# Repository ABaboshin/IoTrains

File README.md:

# IoTrains

Internet of Trains :)

The existing systems in the market are either with old roots (DCC) or not opensource (Märklin). More then that they were built over 20 years ago and therefore have historical restrictions. In order to be able more flexible I started to write a firmware for the trains and accessories using ESP32/ESP8266.

The projects consists of:
 - [Firmware](./firmware/) which is written in c++ using PlatformIO,
 - MQTT Broker, see [emqx](./emqx) as an example,
 - A [backend](./webui/server) written in typesript,
 - as well [frontend](./webui/client/) in react,
 - [json schema](./jsonschema/) describes a mqtt based protocol.

# License
The source code and schematic are licensed under MIT license.

The train's STL files are licensed under CC BY-NC-SA 4.0.

# Notes
 - Connect an audio amplifier to an i2s capable pin i.e. DAC_1.

## TODO
 - multiple rfid
 - responsive ui / refresh on update
 - process rfid events
 - sqlite3
 - main board max 4 x 2.3 c

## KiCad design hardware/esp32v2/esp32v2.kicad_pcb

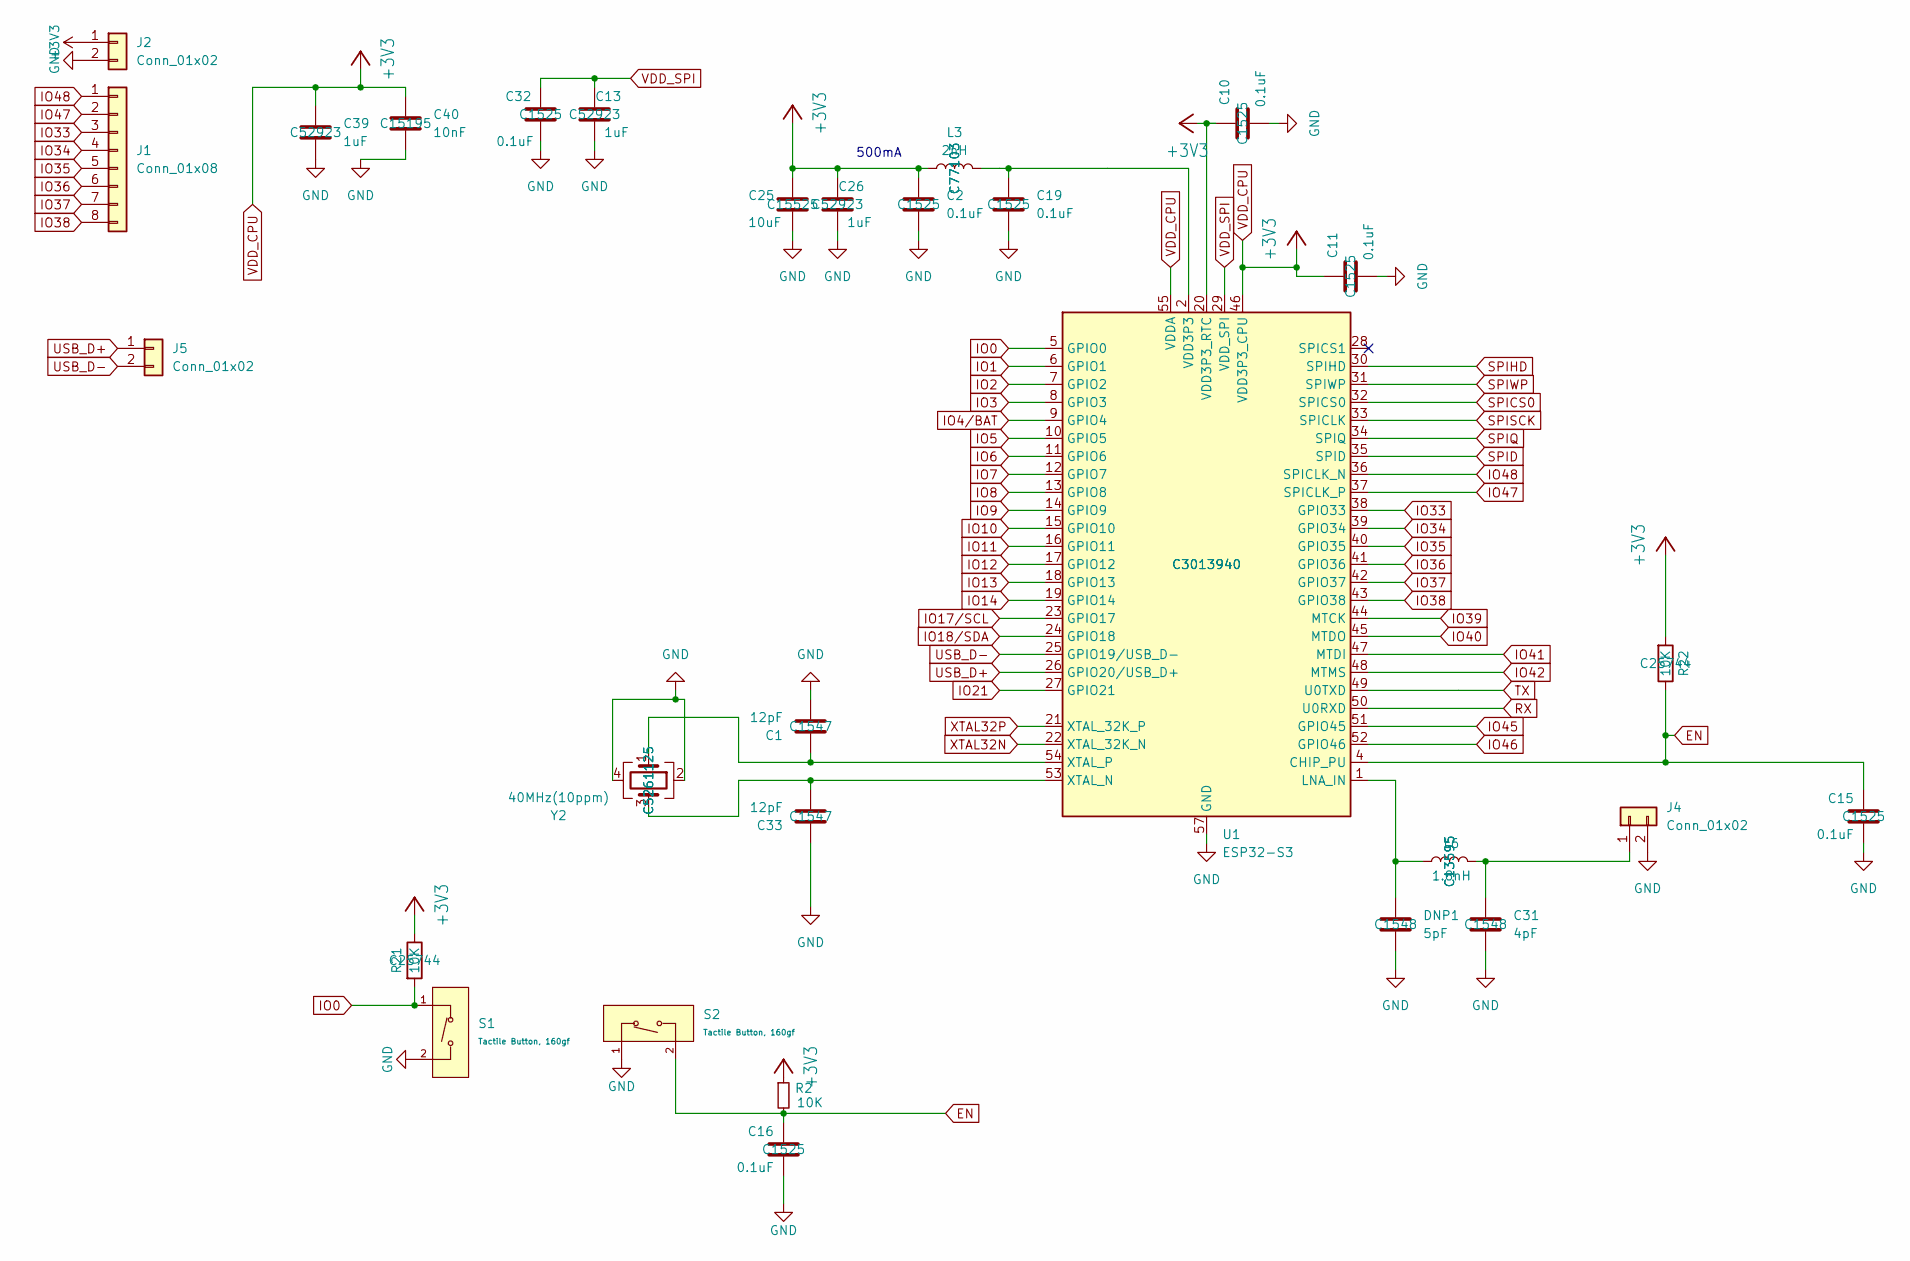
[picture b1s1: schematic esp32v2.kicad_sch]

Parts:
C1, C33: 12pF; C_0201_0603Metric; MNF PART NUMBER C1547; LCSC C1547
C2, C10, C11, C15, C16, C19, C32: 0.1uF; C_0201_0603Metric; MNF PART NUMBER C1525; LCSC C1525
C13, C26, C39: 1uF; C_0201_0603Metric; MNF PART NUMBER C52923; LCSC C52923
C25: 10uF; C_0201_0603Metric; MNF PART NUMBER C15525; LCSC C15525
C31: 4pF; C_0201_0603Metric; MNF PART NUMBER C1548; LCSC C1548
C40: 10nF; C_0201_0603Metric; MNF PART NUMBER C15195; LCSC C15195
DNP1: 5pF; C_0201_0603Metric; MNF PART NUMBER C1548; LCSC C1548
J1: Conn_01x08; JST_SHL_SM08B-SHLS-TF_1x08-1MP_P1.00mm_Horizontal
J2: Conn_01x02; S2BZRLFSN; LCSC C157930
J4: Conn_01x02; U.FL_Molex_MCRF_73412-0110_Vertical
J5: Conn_01x02; JST_SH_BM02B-SRSS-TB_1x02-1MP_P1.00mm_Vertical; LCSC C157930
L3: 2nH; L_0201_0603Metric; MNF PART NUMBER C77103; LCSC C77103
L6: 1.8nH; L_0201_0603Metric; MNF PART NUMBER C13595; LCSC C13595
R2: 10K; R_0201_0603Metric
R21, R22: 10K; R_0201_0603Metric; MNF PART NUMBER C25744; LCSC C25744
S1, S2: Tactile Button, 160gf; SW_TS-1088-AR02016; Voltage Rating (Dc) 12V; Part TS-1088-AR02016; LCSC C720477
U1: ESP32-S3; QFN-56-1EP_7x7mm_P0.4mm_EP4x4mm; MNF PART NUMBER C3013940; LCSC C3013940
Y2: 40MHz(10ppm); Crystal_SMD_2520-4Pin_2.5x2.0mm; MNF PART NUMBER C5261125; LCSC C5261125

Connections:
EN: C15.1, C16.1, R2.2, R22.1, S2.2 (B), U1.4 (CHIP_PU)
GND: C1.2, C2.2, C10.2, C11.2, C13.2, C15.2, C16.2, C19.2, C25.2, C26.2, C31.2, C32.2, C33.1, C39.2, C40.2, DNP1.2, J2.2, J4.2, S1.2 (B), S2.1 (A), U1.57 (GND), Y2.2, Y2.4
IO0: R21.2, S1.1 (A), U1.5 (GPIO0)
IO1: U1.6 (GPIO1)
IO2: U1.7 (GPIO2)
IO3: U1.8 (GPIO3)
IO4/BAT: U1.9 (GPIO4)
IO5: U1.10 (GPIO5)
IO6: U1.11 (GPIO6)
IO7: U1.12 (GPIO7)
IO8: U1.13 (GPIO8)
IO9: U1.14 (GPIO9)
IO10: U1.15 (GPIO10)
IO11: U1.16 (GPIO11)
IO12: U1.17 (GPIO12)
IO13: U1.18 (GPIO13)
IO14: U1.19 (GPIO14)
IO17/SCL: U1.23 (GPIO17)
IO18/SDA: U1.24 (GPIO18)
IO21: U1.27 (GPIO21)
IO33: J1.3, U1.38 (GPIO33)
IO34: J1.4, U1.39 (GPIO34)
IO35: J1.5, U1.40 (GPIO35)
IO36: J1.6, U1.41 (GPIO36)
IO37: J1.7, U1.42 (GPIO37)
IO38: J1.8, U1.43 (GPIO38)
IO39: U1.44 (MTCK)
IO40: U1.45 (MTDO)
IO41: U1.47 (MTDI)
IO42: U1.48 (MTMS)
IO45: U1.51 (GPIO45)
IO46: U1.52 (GPIO46)
IO47: J1.2, U1.37 (SPICLK_P)
IO48: J1.1, U1.36 (SPICLK_N)
unnamed: C19.1, L3.2, U1.2 (VDD3P3), U1.3 (VDD3P3)
unnamed: C31.1, J4.1, L6.2
unnamed: DNP1.1, L6.1, U1.1 (LNA_IN)
unnamed: C33.2, U1.53 (XTAL_N), Y2.3
unnamed: C1.1, U1.54 (XTAL_P), Y2.1
RX: U1.50 (U0RXD)
SPICS0: U1.32 (SPICS0)
SPID: U1.35 (SPID)
SPIHD: U1.30 (SPIHD)
SPIQ: U1.34 (SPIQ)
SPISCK: U1.33 (SPICLK)
SPIWP: U1.31 (SPIWP)
TX: U1.49 (U0TXD)
USB_D+: J5.1, U1.26 (GPIO20/USB_D+)
USB_D-: J5.2, U1.25 (GPIO19/USB_D-)
VDD_CPU: C2.1, C10.1, C11.1, C25.1, C26.1, C39.1, C40.1, J2.1, L3.1, R2.1, R21.1, R22.2, U1.20 (VDD3P3_RTC), U1.46 (VDD3P3_CPU), U1.55 (VDDA), U1.56 (VDDA)
VDD_SPI: C13.1, C32.1, U1.29 (VDD_SPI)
XTAL32N: U1.22 (XTAL_32K_N)
XTAL32P: U1.21 (XTAL_32K_P)

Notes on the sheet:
500mA

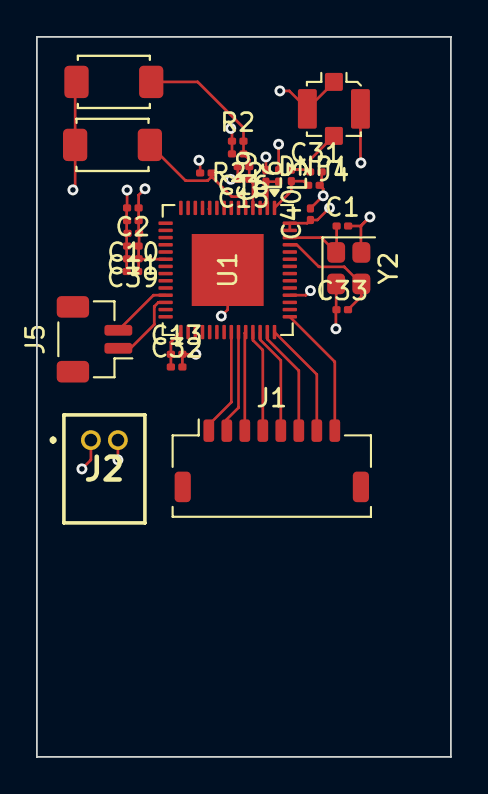
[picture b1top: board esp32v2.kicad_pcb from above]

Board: 4 copper layers, 23.0 x 40.0 mm, 29 parts (0 on the bottom side), 20 nets.

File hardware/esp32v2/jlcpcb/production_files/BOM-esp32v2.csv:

Comment,Designator,Footprint,LCSC,Quantity
0.1uF,"C10,C11,C15,C16,C19,C2,C32",C_0201_0603Metric,C1525,7
1.8nH,L6,L_0201_0603Metric,C13595,1
10K,"R21,R22",R_0201_0603Metric,C25744,2
10nF,C40,C_0201_0603Metric,C15195,1
10uF,C25,C_0201_0603Metric,C15525,1
12pF,"C1,C33",C_0201_0603Metric,C1547,2
1uF,"C13,C26,C39",C_0201_0603Metric,C52923,3
2nH,L3,L_0201_0603Metric,C77103,1
40MHz(10ppm),Y2,Crystal_SMD_2520-4Pin_2.5x2.0mm,C5261125,1
4pF,C31,C_0201_0603Metric,C1548,1
5pF,DNP1,C_0201_0603Metric,C1548,1
Conn_01x02,"J2,J5",S2BZRLFSN,C157930,2
ESP32-S3,U1,QFN-56-1EP_7x7mm_P0.4mm_EP4x4mm,C2913194,1
"Tactile Button, 160gf","S1,S2",SW_TS-1088-AR02016,C720477,2
10K,R2,R_0201_0603Metric,,1
Conn_01x08,J1,JST_SHL_SM08B-SHLS-TF_1x08-1MP_P1.00mm_Horizontal,,1
Conn_01x02,J4,U.FL_Molex_MCRF_73412-0110_Vertical,,1

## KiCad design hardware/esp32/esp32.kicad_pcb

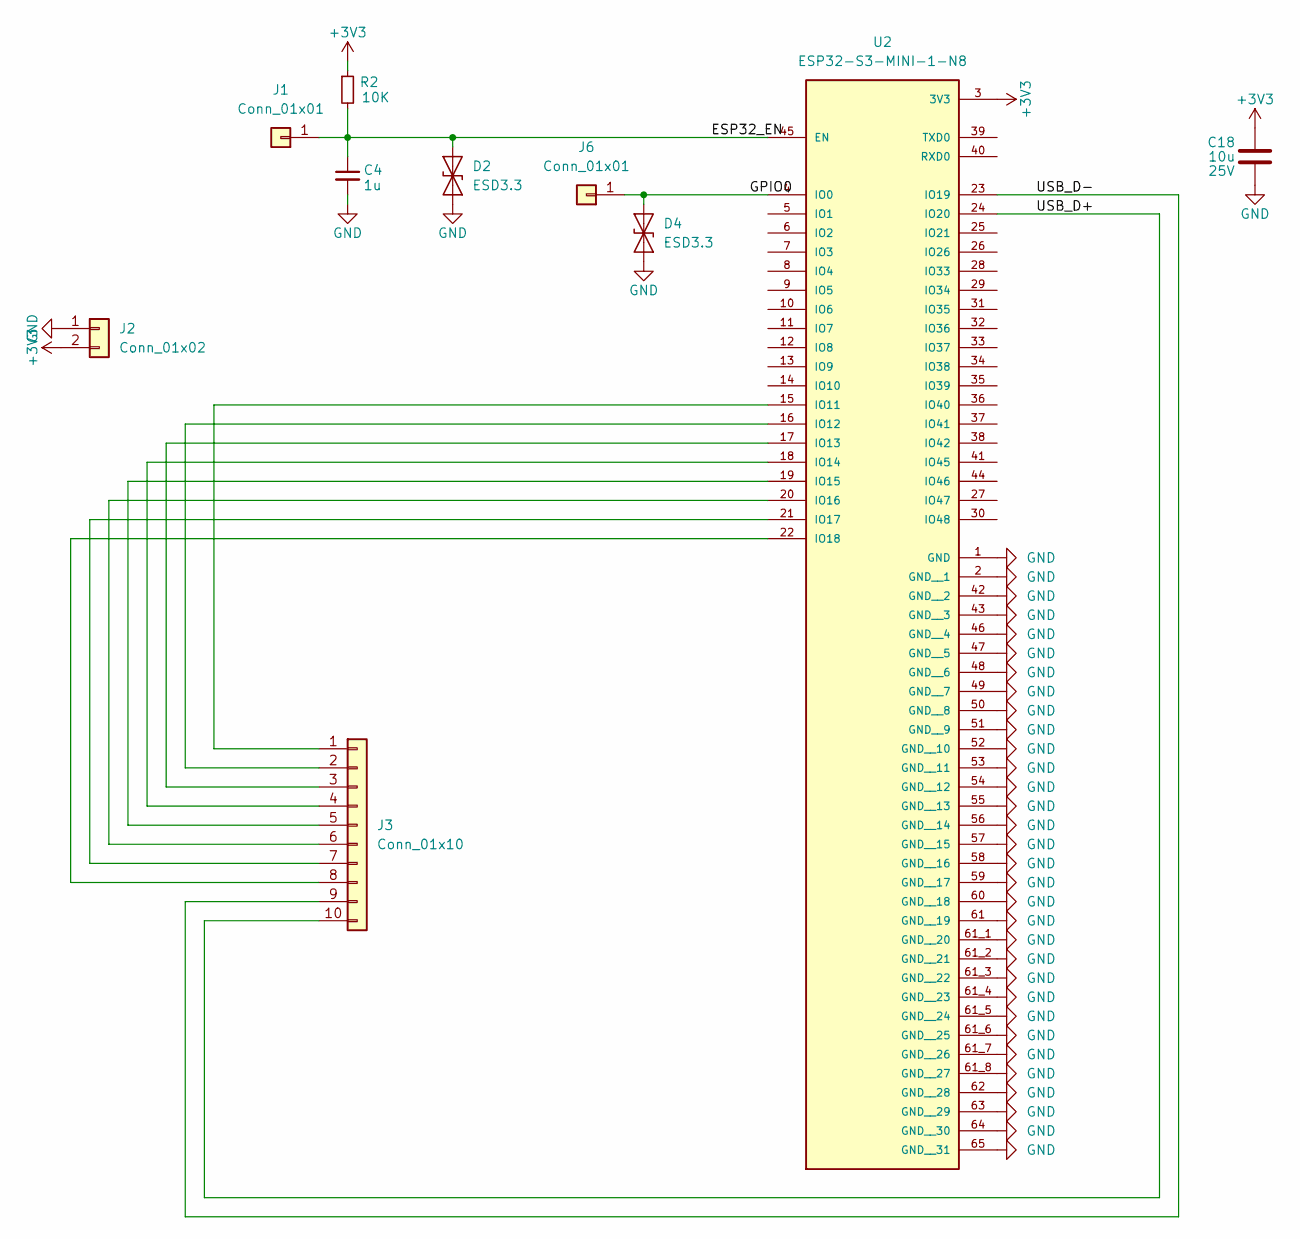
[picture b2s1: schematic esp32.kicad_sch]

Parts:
C4: 1u; C_0603_1608Metric
C18: 10u; C_0603_1608Metric; Voltage 25V; LCSC Part # C96446
D2, D4: ESD3.3; SOT-723
J1, J6: Conn_01x01; PinHeader_1x01_P1.00mm_Vertical
J2: Conn_01x02; S2BZRLFSN; LCSC C157930
J3: Conn_01x10; SM10B-SRSS-TB; LCSC C160409
R2: 10K; R_0402_1005Metric
U2: ESP32-S3-MINI-1-N8; XCVR_ESP32-S3-MINI-1-N8; PARTREV v0.6

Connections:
+3V3: C18.1, J2.2, R2.1, U2.3 (3V3)
/ESP32_EN: C4.1, D2.2 (A2), J1.1, R2.2, U2.45 (EN)
/GPIO0: D4.2 (A2), J6.1, U2.4 (IO0)
/USB_D+: J3.10, U2.24 (IO20)
/USB_D-: J3.9, U2.23 (IO19)
GND: C4.2, C18.2, D2.1 (A1), D4.1 (A1), J2.1, U2.1 (GND), U2.2 (GND__1), U2.42 (GND__2), U2.43 (GND__3), U2.46 (GND__4), U2.47 (GND__5), U2.48 (GND__6), U2.49 (GND__7), U2.50 (GND__8), U2.51 (GND__9), U2.52 (GND__10), U2.53 (GND__11), U2.54 (GND__12), U2.55 (GND__13), U2.56 (GND__14), U2.57 (GND__15), U2.58 (GND__16), U2.59 (GND__17), U2.60 (GND__18), U2.61 (GND__19), U2.61_1 (GND__20), U2.61_2 (GND__21), U2.61_3 (GND__22), U2.61_4 (GND__23), U2.61_5 (GND__24), U2.61_6 (GND__25), U2.61_7 (GND__26), U2.61_8 (GND__27), U2.62 (GND__28), U2.63 (GND__29), U2.64 (GND__30), U2.65 (GND__31)
unnamed: J3.1, U2.15 (IO11)
unnamed: J3.2, U2.16 (IO12)
unnamed: J3.3, U2.17 (IO13)
unnamed: J3.4, U2.18 (IO14)
unnamed: J3.5, U2.19 (IO15)
unnamed: J3.6, U2.20 (IO16)
unnamed: J3.7, U2.21 (IO17)
unnamed: J3.8, U2.22 (IO18)

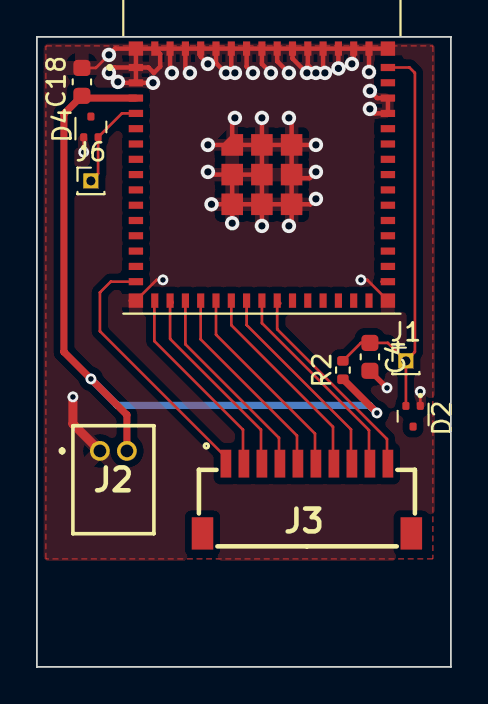
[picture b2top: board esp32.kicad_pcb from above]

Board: 2 copper layers, 23.0 x 35.0 mm, 10 parts (0 on the bottom side), 14 nets.

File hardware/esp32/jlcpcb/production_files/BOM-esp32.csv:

Comment,Designator,Footprint,LCSC,Quantity
10K,R2,R_0402_1005Metric,C25744,1
10u,C18,C_0603_1608Metric,C96446,1
1u,C4,C_0603_1608Metric,C15849,1
Conn_01x02,J2,S2BZRLFSN,C157930,1
Conn_01x10,J3,SM10B-SRSS-TB,C160409,1
ESD3.3,"D2,D4",SOT-723,C233435,2
ESP32-S3-MINI-1-N8,U2,XCVR_ESP32-S3-MINI-1-N8,C2913206,1
Conn_01x01,J1,PinHeader_1x01_P1.00mm_Vertical,,1
Conn_01x01,J6,PinHeader_1x01_P1.00mm_Vertical,,1

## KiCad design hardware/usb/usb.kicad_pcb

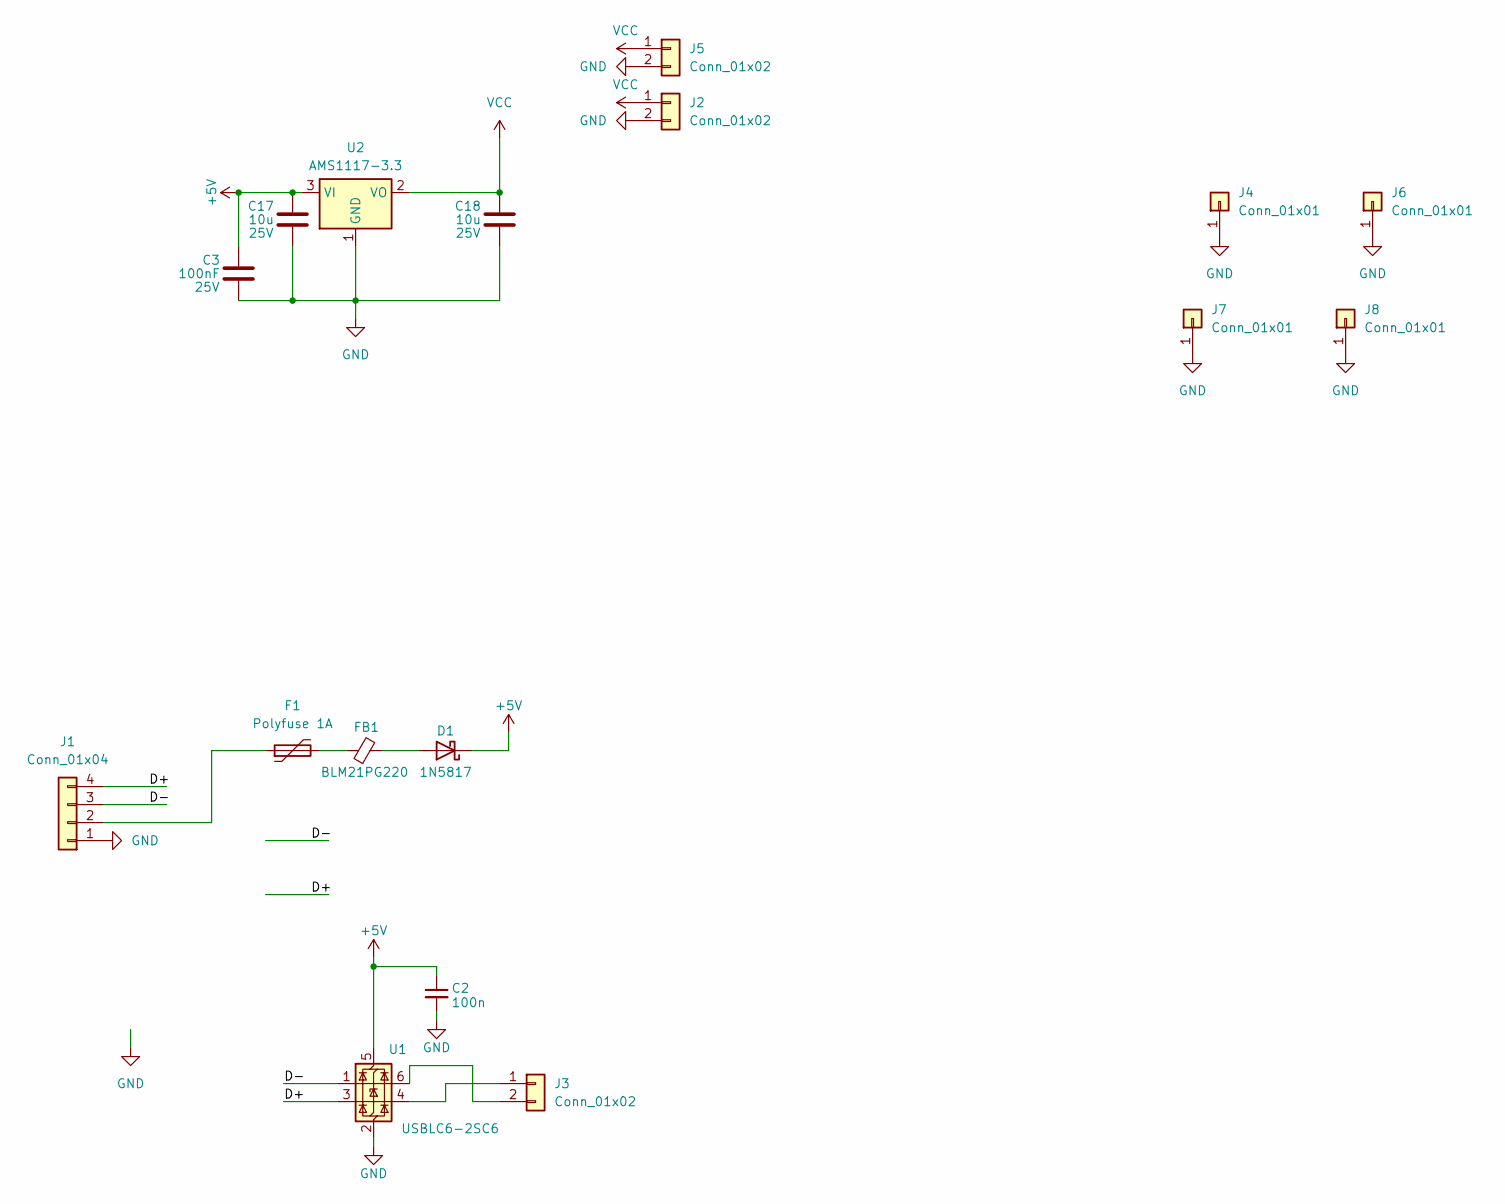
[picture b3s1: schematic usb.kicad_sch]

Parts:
C2: 100n; C_0402_1005Metric_Pad0.74x0.62mm_HandSolder
C3: 100nF; C_0603_1608Metric; Voltage 25V; LCSC Part # C96446
C17, C18: 10u; C_0603_1608Metric; Voltage 25V; LCSC Part # C96446
D1: 1N5817; SOD2613X110N; LCSC C2828424
F1: Polyfuse 1A; Fuse_1206_3216Metric
FB1: BLM21PG220; L_0805_2012Metric
J1: Conn_01x04; PinHeader_1x04_P2.54mm_Vertical
J2, J5: Conn_01x02; S2BZRLFSN; LCSC C157930
J3: Conn_01x02; JST_SHL_SM02B-SHLS-TF_1x02-1MP_P1.00mm_Horizontal; LCSC C160402
J4, J6, J7, J8: Conn_01x01; PinHeader_1x01_P1.00mm_Vertical
U1: USBLC6-2SC6; SOT-23-6
U2: AMS1117-3.3; SOT-89-3; LCSC Part # C7473143

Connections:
+5V: C2.1, C3.1, C17.1, D1.1 (K), U1.5 (VBUS), U2.3 (VI)
/D+: J1.4, U1.3 (I/O2)
/D-: J1.3, U1.1 (I/O1)
GND: C2.2, C3.2, C17.2, C18.2, J1.1, J2.2, J4.1, J5.2, J6.1, J7.1, J8.1, U1.2 (GND), U2.1 (GND)
unnamed: D1.2 (A), FB1.2
unnamed: F1.2, FB1.1
unnamed: F1.1, J1.2
unnamed: J3.1, U1.4 (I/O2)
unnamed: J3.2, U1.6 (I/O1)
VCC: C18.1, J2.1, J5.1, U2.2 (VO)

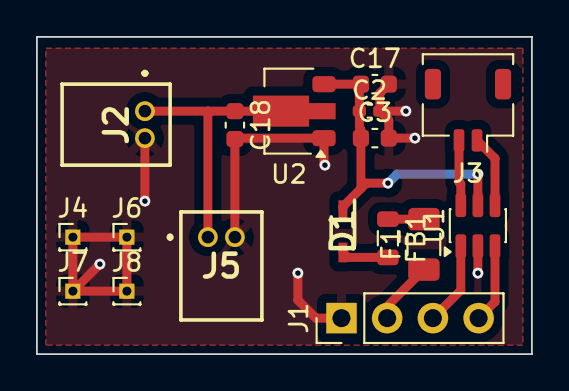
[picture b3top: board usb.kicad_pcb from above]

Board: 2 copper layers, 27.5 x 17.6 mm, 17 parts (0 on the bottom side), 10 nets.

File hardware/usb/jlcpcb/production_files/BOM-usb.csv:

Comment,Designator,Footprint,LCSC,Quantity
100n,C2,C_0402_1005Metric_Pad0.74x0.62mm_HandSolder,C1525,1
100nF,C3,C_0603_1608Metric,C14663,1
10u,"C17,C18",C_0603_1608Metric,C96446,2
1N5817,D1,SOD2613X110N,C2828424,1
AMS1117-3.3,U2,SOT-89-3,C7473143,1
BLM21PG220,FB1,L_0805_2012Metric,C88993,1
Conn_01x02,"J2,J5",S2BZRLFSN,C157930,2
Conn_01x02,J3,JST_SHL_SM02B-SHLS-TF_1x02-1MP_P1.00mm_Horizontal,C160402,1
Polyfuse 1A,F1,Fuse_1206_3216Metric,C1020,1
USBLC6-2SC6,U1,SOT-23-6,C2687116,1
Conn_01x04,J1,PinHeader_1x04_P2.54mm_Vertical,,1
Conn_01x01,J8,PinHeader_1x01_P1.00mm_Vertical,,1
Conn_01x01,J7,PinHeader_1x01_P1.00mm_Vertical,,1
Conn_01x01,J6,PinHeader_1x01_P1.00mm_Vertical,,1
Conn_01x01,J4,PinHeader_1x01_P1.00mm_Vertical,,1

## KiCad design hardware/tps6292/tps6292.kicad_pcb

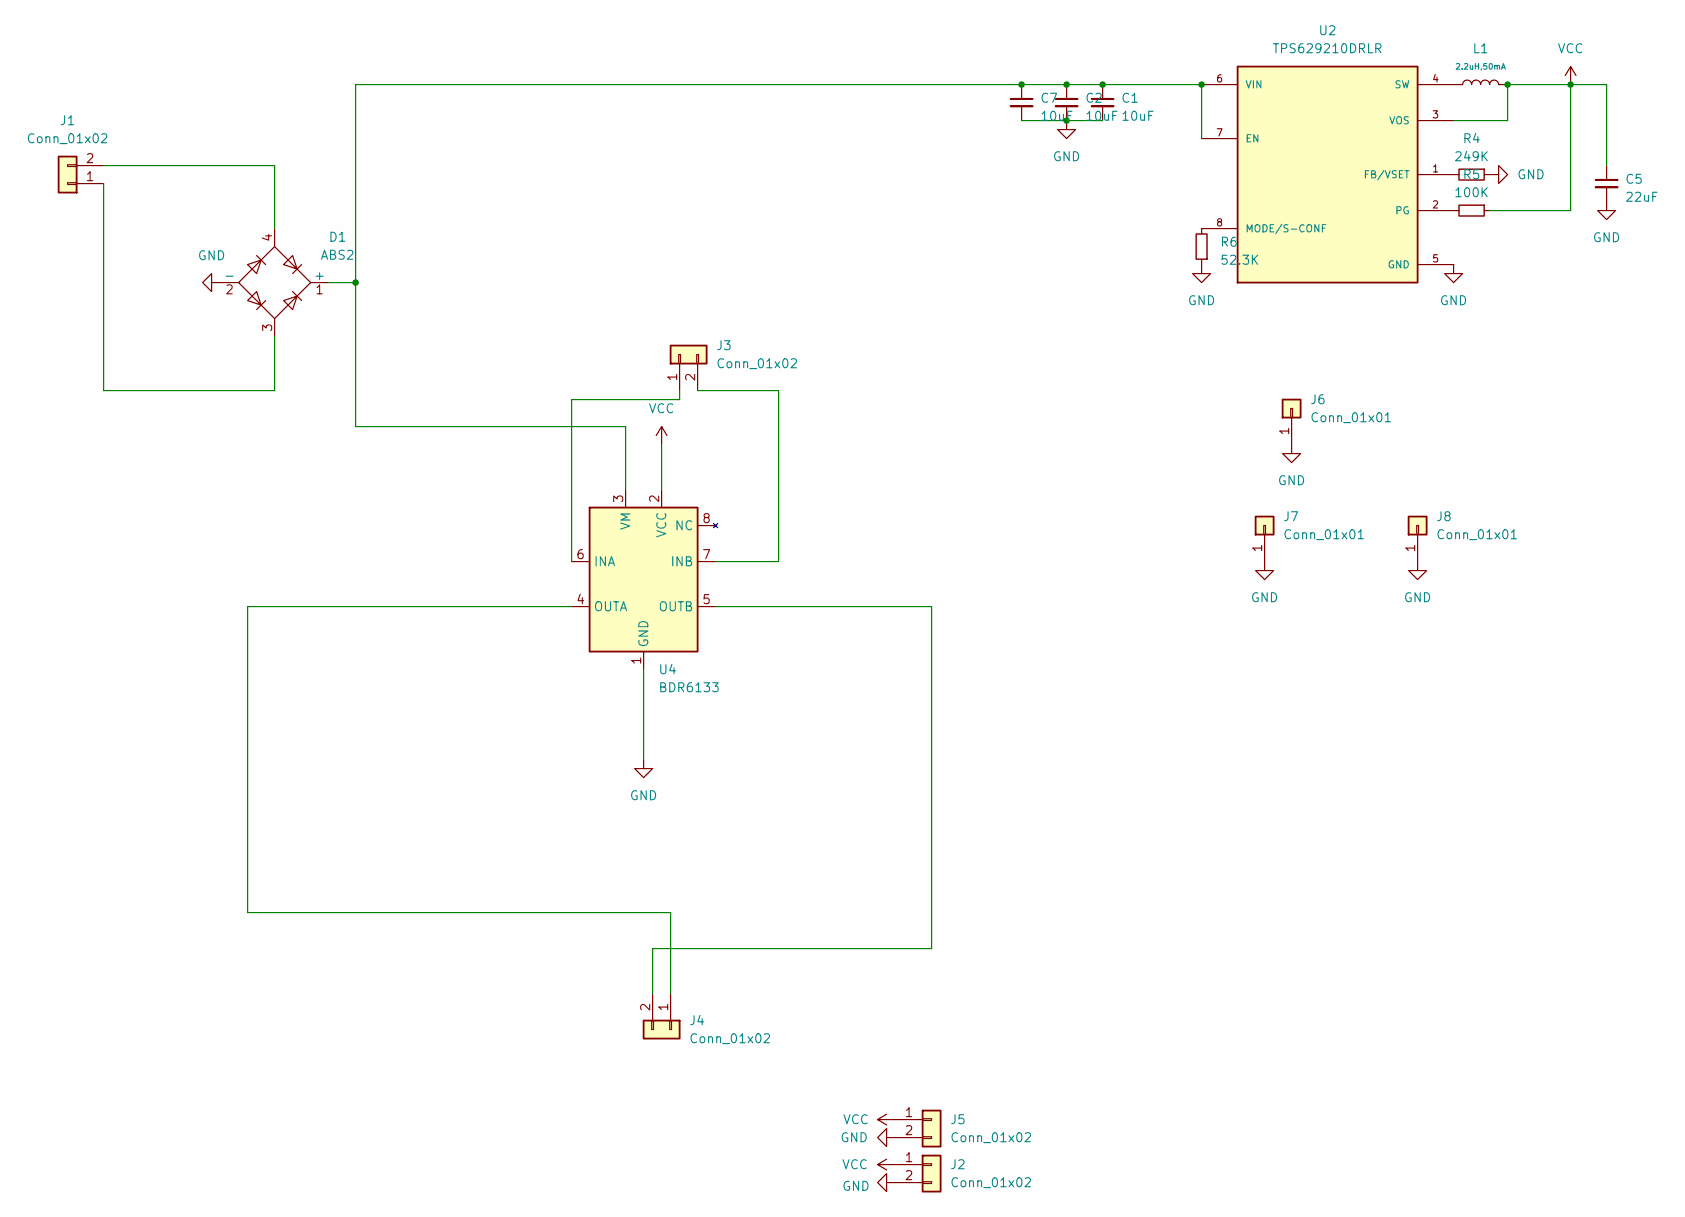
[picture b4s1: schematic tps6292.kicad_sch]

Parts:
C1, C2, C7: 10uF; C_0603_1608Metric; LCSC C96446
C5: 22uF; C_0603_1608Metric; LCSC C59461
D1: ABS2; Diode_Bridge_Diotec_ABS
J1, J2, J4, J5: Conn_01x02; S2BZRLFSN; LCSC C157930
J3: Conn_01x02; JST_SHL_SM02B-SHLS-TF_1x02-1MP_P1.00mm_Horizontal; LCSC C160402
J6, J7, J8: Conn_01x01; PinHeader_1x01_P1.00mm_Vertical
L1: 2.2uH,50mA; L_0805; Tolerance ±10%; Part CMI201209U2R2KT; LCSC C1043
R4: 249K; R_0603_1608Metric; LCSC C22918
R5: 100K; R_0603_1608Metric; LCSC C25803
R6: 52.3K; R_0603_1608Metric; LCSC C23198
U2: TPS629210DRLR; SOT50P160X60-8N; PARTREV B; LCSC C5219301
U4: BDR6133; SOIC-8-1EP_3.9x4.9mm_P1.27mm_EP2.41x3.3mm_ThermalVias; LCSC Part # C2687793

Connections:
GND: C1.2, C2.2, C5.2, C7.2, D1.2 (-), J2.2, J5.2, J6.1, J7.1, J8.1, R4.1, R6.1, U2.5 (GND), U4.1 (GND), U4.9 (GND)
unnamed: C1.1, C2.1, C7.1, D1.1 (+), U2.6 (VIN), U2.7 (EN), U4.3 (VM)
unnamed: D1.3, J1.1
unnamed: D1.4, J1.2
unnamed: J3.1, U4.6 (INA)
unnamed: J3.2, U4.7 (INB)
unnamed: J4.1, U4.4 (OUTA)
unnamed: J4.2, U4.5 (OUTB)
unnamed: R4.2, U2.1 (FB/VSET)
unnamed: R6.2, U2.8 (MODE/S-CONF)
unnamed: R5.2, U2.2 (PG)
unnamed: L1.1, U2.4 (SW)
VCC: C5.1, J2.1, J5.1, L1.2, R5.1, U2.3 (VOS), U4.2 (VCC)

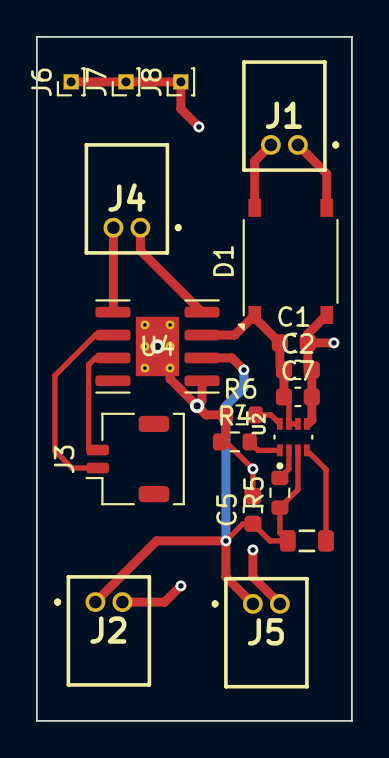
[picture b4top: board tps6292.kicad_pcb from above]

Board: 2 copper layers, 17.5 x 38.0 mm, 19 parts (0 on the bottom side), 13 nets.

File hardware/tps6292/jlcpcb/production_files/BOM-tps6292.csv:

Comment,Designator,Footprint,LCSC,Quantity
100K,R5,R_0603_1608Metric,C25803,1
10uF,"C1,C2,C7",C_0603_1608Metric,C96446,3
"2.2uH,50mA",L1,L_0805,C1043,1
22uF,C5,C_0603_1608Metric,C59461,1
249K,R4,R_0603_1608Metric,C22918,1
52.3K,R6,R_0603_1608Metric,C23198,1
ABS2,D1,Diode_Bridge_Diotec_ABS,C84159,1
BDR6133,U4,SOIC-8-1EP_3.9x4.9mm_P1.27mm_EP2.41x3.3mm_ThermalVias,C2687793,1
Conn_01x02,"J1,J2,J4,J5",JST_ZH_S2B-ZR-SM4A-TF_1x02-1MP_P1.50mm_Horizontal,C157930,4
Conn_01x02,J3,JST_SHL_SM02B-SHLS-TF_1x02-1MP_P1.00mm_Horizontal,C160402,1
TPS629210DRLR,U2,SOT50P160X60-8N,C5219301,1
Conn_01x01,J8,PinHeader_1x01_P1.00mm_Vertical,,1
Conn_01x01,J7,PinHeader_1x01_P1.00mm_Vertical,,1
Conn_01x01,J6,PinHeader_1x01_P1.00mm_Vertical,,1

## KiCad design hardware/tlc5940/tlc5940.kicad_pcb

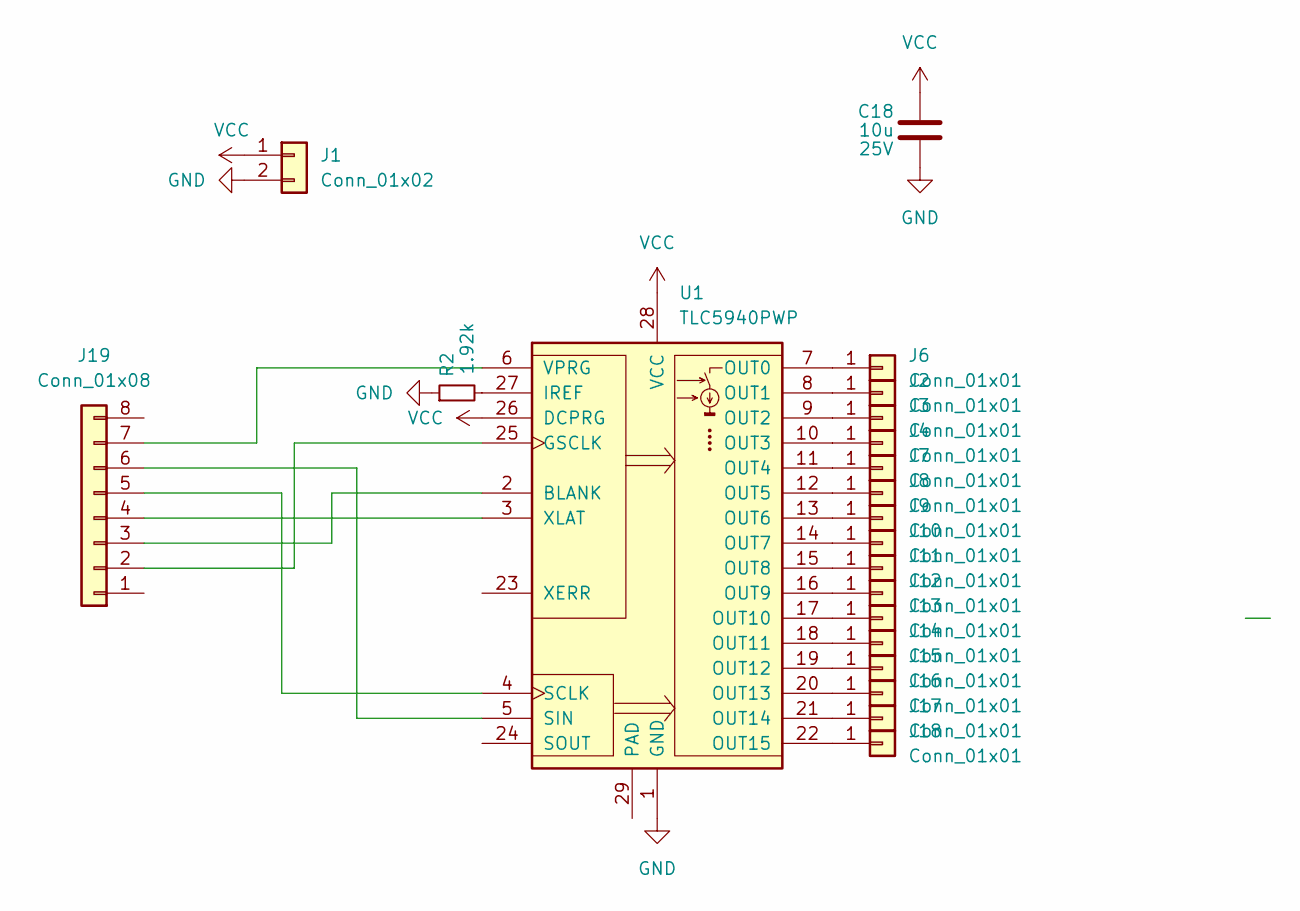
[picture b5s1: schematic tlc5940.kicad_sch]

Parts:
C18: 10u; C_0603_1608Metric; Voltage 25V; LCSC Part # C96446
J1: Conn_01x02; S2BZRLFSN; LCSC C157930
J2, J3, J4, J6, J7, J8, J9, J10, J11, J12, J13, J14, J15, J16, J17, J18: Conn_01x01; PinHeader_1x01_P1.00mm_Vertical
J19: Conn_01x08; JST_SHL_SM08B-SHLS-TF_1x08-1MP_P1.00mm_Horizontal
R2: 1.92k; R_0402_1005Metric
U1: TLC5940PWP; HTSSOP-28-1EP_4.4x9.7mm_P0.65mm_EP3.4x9.5mm_Mask2.4x6.17mm_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

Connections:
GND: C18.2, J1.2, R2.1, U1.1 (GND)
unnamed: J2.1, U1.8 (OUT1)
unnamed: J3.1, U1.9 (OUT2)
unnamed: J4.1, U1.10 (OUT3)
unnamed: J6.1, U1.7 (OUT0)
unnamed: J7.1, U1.11 (OUT4)
unnamed: J8.1, U1.12 (OUT5)
unnamed: J9.1, U1.13 (OUT6)
unnamed: J10.1, U1.14 (OUT7)
unnamed: J11.1, U1.15 (OUT8)
unnamed: J12.1, U1.16 (OUT9)
unnamed: J13.1, U1.17 (OUT10)
unnamed: J14.1, U1.18 (OUT11)
unnamed: J15.1, U1.19 (OUT12)
unnamed: J16.1, U1.20 (OUT13)
unnamed: J17.1, U1.21 (OUT14)
unnamed: J18.1, U1.22 (OUT15)
unnamed: J19.2, U1.25 (GSCLK)
unnamed: J19.3, U1.2 (BLANK)
unnamed: J19.4, U1.3 (XLAT)
unnamed: J19.5, U1.4 (SCLK)
unnamed: J19.6, U1.5 (SIN)
unnamed: J19.7, U1.6 (VPRG)
unnamed: R2.2, U1.27 (IREF)
VCC: C18.1, J1.1, U1.26 (DCPRG), U1.28 (VCC)

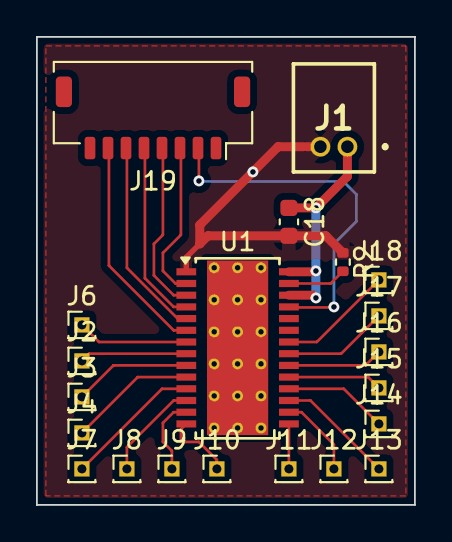
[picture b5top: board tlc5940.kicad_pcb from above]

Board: 2 copper layers, 21.0 x 26.0 mm, 21 parts (0 on the bottom side), 25 nets.

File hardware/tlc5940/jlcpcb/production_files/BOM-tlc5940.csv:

Comment,Designator,Footprint,LCSC,Quantity
1.92k,R2,R_0402_1005Metric,C4109,1
10u,C18,C_0603_1608Metric,C96446,1
Conn_01x02,J1,S2BZRLFSN,C157930,1
Conn_01x08,J19,JST_SHL_SM08B-SHLS-TF_1x08-1MP_P1.00mm_Horizontal,C160407,1
TLC5940PWP,U1,HTSSOP-28-1EP_4.4x9.7mm_P0.65mm_EP3.4x9.5mm_Mask2.4x6.17mm_ThermalVias,C181653,1
Conn_01x01,J3,PinHeader_1x01_P1.00mm_Vertical,,1
Conn_01x01,J2,PinHeader_1x01_P1.00mm_Vertical,,1
Conn_01x01,J18,PinHeader_1x01_P1.00mm_Vertical,,1
Conn_01x01,J17,PinHeader_1x01_P1.00mm_Vertical,,1
Conn_01x01,J16,PinHeader_1x01_P1.00mm_Vertical,,1
Conn_01x01,J15,PinHeader_1x01_P1.00mm_Vertical,,1
Conn_01x01,J14,PinHeader_1x01_P1.00mm_Vertical,,1
Conn_01x01,J13,PinHeader_1x01_P1.00mm_Vertical,,1
Conn_01x01,J12,PinHeader_1x01_P1.00mm_Vertical,,1
Conn_01x01,J11,PinHeader_1x01_P1.00mm_Vertical,,1
Conn_01x01,J10,PinHeader_1x01_P1.00mm_Vertical,,1
Conn_01x01,J9,PinHeader_1x01_P1.00mm_Vertical,,1
Conn_01x01,J8,PinHeader_1x01_P1.00mm_Vertical,,1
Conn_01x01,J7,PinHeader_1x01_P1.00mm_Vertical,,1
Conn_01x01,J4,PinHeader_1x01_P1.00mm_Vertical,,1
Conn_01x01,J6,PinHeader_1x01_P1.00mm_Vertical,,1

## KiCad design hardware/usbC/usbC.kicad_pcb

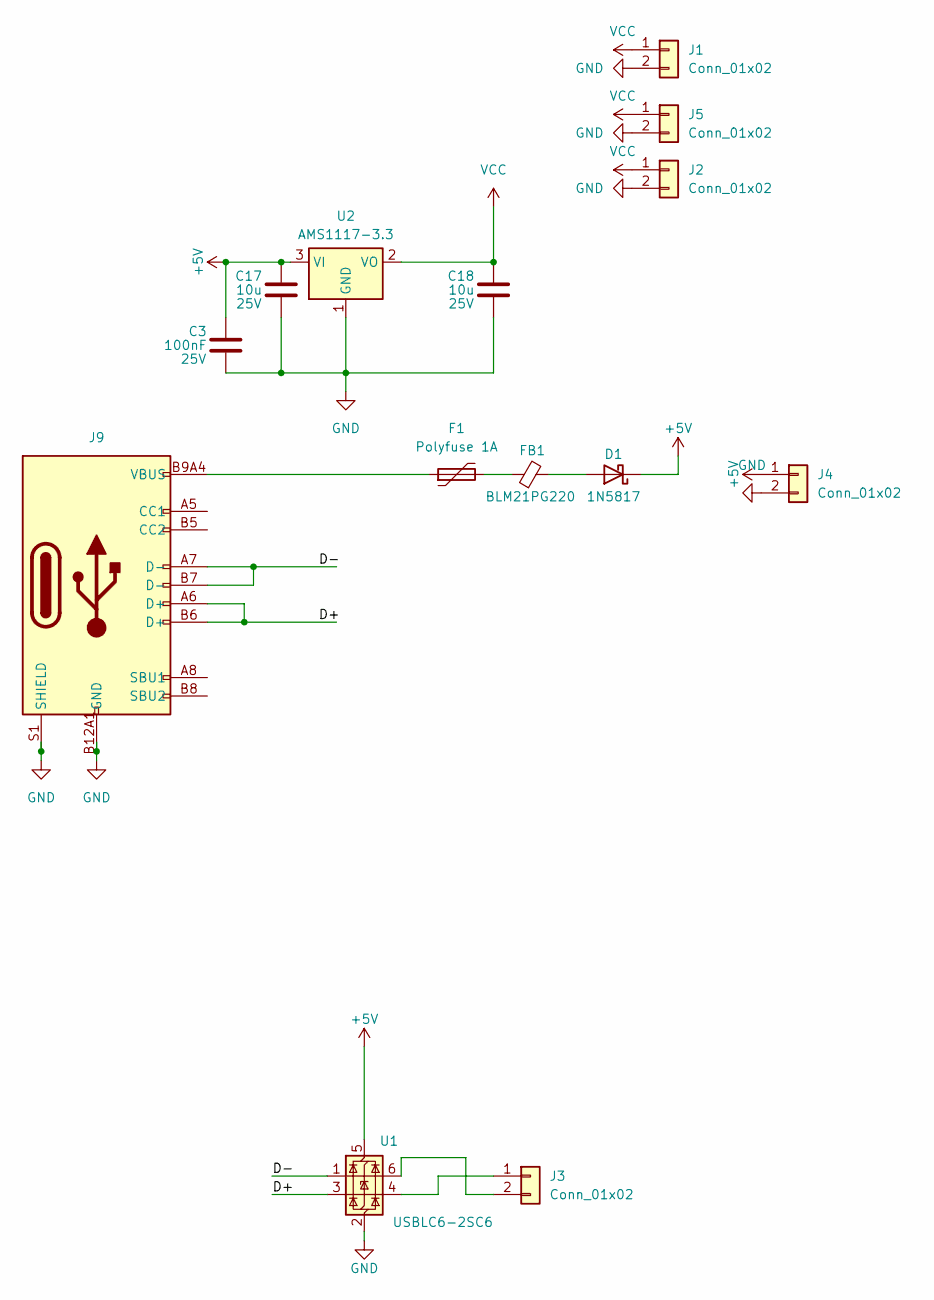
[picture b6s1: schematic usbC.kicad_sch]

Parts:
C3: 100nF; C_0603_1608Metric; Voltage 25V; LCSC C96446
C17, C18: 10u; C_0603_1608Metric; Voltage 25V; LCSC C96446
D1: 1N5817; SOD2613X110N; LCSC C2828424
F1: Polyfuse 1A; Fuse_1206_3216Metric; LCSC C1020
FB1: BLM21PG220; L_0805_2012Metric; LCSC C88993
J1, J2, J4, J5: Conn_01x02; S2BZRLFSN; LCSC C157930
J3: Conn_01x02; JST_SHL_SM02B-SHLS-TF_1x02-1MP_P1.00mm_Horizontal; LCSC C160402
J9: Connector, USB-TYPE-C-16P; TYPE-C-SMD_HX-TYPE-C-16PIN; LCSC C2927039
U1: USBLC6-2SC6; SOT-23-6; LCSC C2687116
U2: AMS1117-3.3; SOT-89-3; LCSC C7473143

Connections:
+5V: C3.1, C17.1, D1.1 (K), J4.1, U1.5 (VBUS), U2.3 (VI)
/D+: J9.A6 (D+), J9.B6 (D+), U1.3 (I/O2)
/D-: J9.A7 (D-), J9.B7 (D-), U1.1 (I/O1)
GND: C3.2, C17.2, C18.2, J1.2, J2.2, J4.2, J5.2, J9.A12B1 (GND), J9.B12A1 (GND), J9.S1 (SHIELD), U1.2 (GND), U2.1 (GND)
unnamed: D1.2 (A), FB1.2
unnamed: F1.1, J9.A9B4 (VBUS), J9.B9A4 (VBUS)
unnamed: F1.2, FB1.1
unnamed: J3.1, U1.4 (I/O2)
unnamed: J3.2, U1.6 (I/O1)
VCC: C18.1, J1.1, J2.1, J5.1, U2.2 (VO)

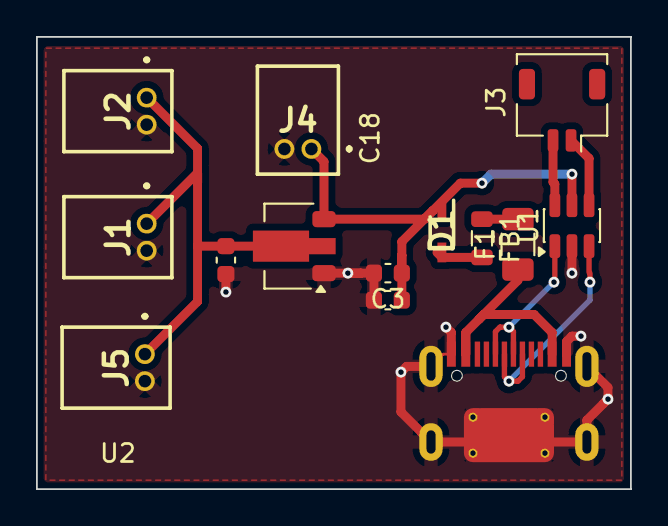
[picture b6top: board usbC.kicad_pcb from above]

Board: 2 copper layers, 33.0 x 25.1 mm, 14 parts (0 on the bottom side), 10 nets.

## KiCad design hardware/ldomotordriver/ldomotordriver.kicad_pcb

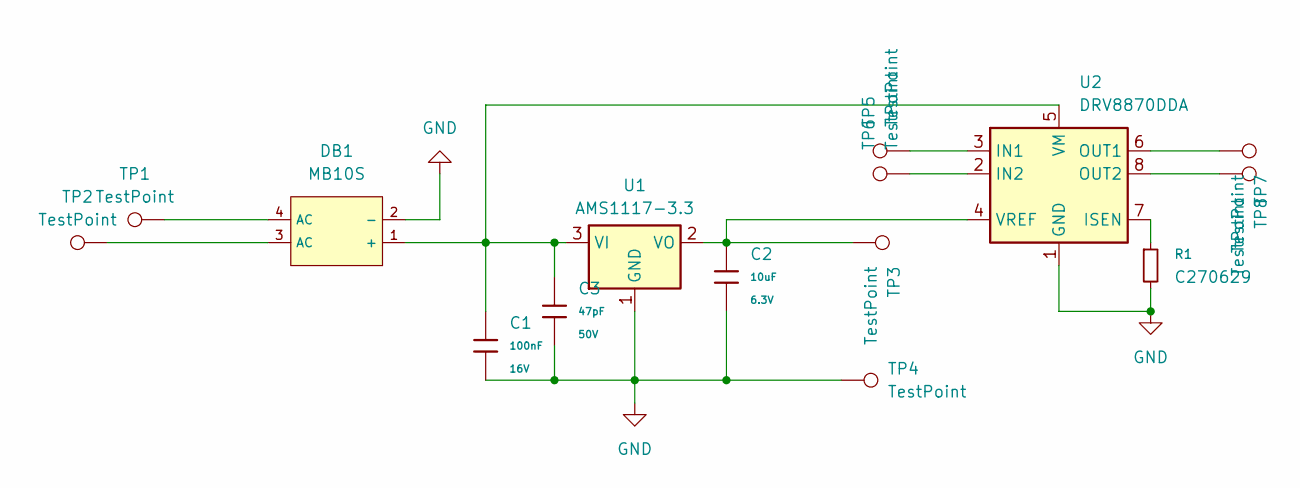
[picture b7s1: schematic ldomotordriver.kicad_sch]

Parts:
C1: 100nF; C_0402; Voltage Rated 16V; Tolerance ±10%; Part CL05B104KO5NNNC; LCSC C1525
C2: 10uF; C_0402; Voltage Rated 6.3V; Tolerance ±20%; Part CL05A106MQ5NUNC; LCSC C15525
C3: 47pF; C_0402; Voltage Rated 50V; Tolerance ±5%; Part 0402CG470J500NT; LCSC C1567
DB1: MB10S; MBS_L4.7-W3.8-P2.40-LS7.0-TL; Reverse Voltage (Vr) 1kV; Forward Voltage (Vf@If) 1.1V@400mA; Part MB10S-50MIL; LCSC C2488
R1: C270629; R_0402
TP1, TP2, TP3, TP4, TP5, TP6, TP7, TP8: TestPoint; TestPoint_THTPad_1.5x1.5mm_Drill0.7mm
U1: AMS1117-3.3; SOT-223-3_TabPin2
U2: DRV8870DDA; Texas_HTSOP-8-1EP_3.9x4.9mm_P1.27mm_EP2.95x4.9mm_Mask2.4x3.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

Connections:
GND: C1.2, C2.2, C3.2, DB1.2 (-), R1.2, TP4.1, U1.1 (GND), U2.1 (GND), U2.9 (GND)
unnamed: C1.1, C3.1, DB1.1 (+), U1.3 (VI), U2.5 (VM)
unnamed: DB1.3 (AC), TP2.1
unnamed: DB1.4 (AC), TP1.1
unnamed: C2.1, TP3.1, U1.2 (VO), U2.4 (VREF)
unnamed: TP5.1, U2.3 (IN1)
unnamed: TP6.1, U2.2 (IN2)
unnamed: R1.1, U2.7 (ISEN)
unnamed: TP7.1, U2.6 (OUT1)
unnamed: TP8.1, U2.8 (OUT2)

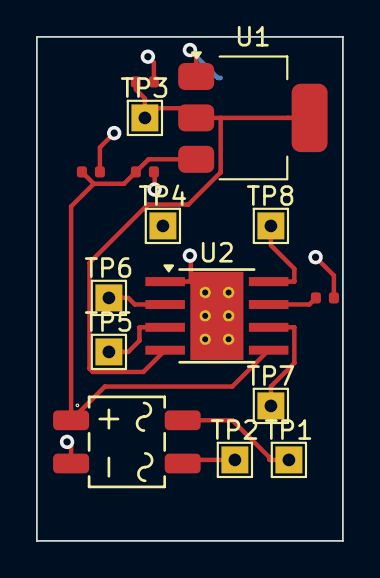
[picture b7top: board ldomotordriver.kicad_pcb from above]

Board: 2 copper layers, 17.0 x 28.0 mm, 15 parts (0 on the bottom side), 10 nets.

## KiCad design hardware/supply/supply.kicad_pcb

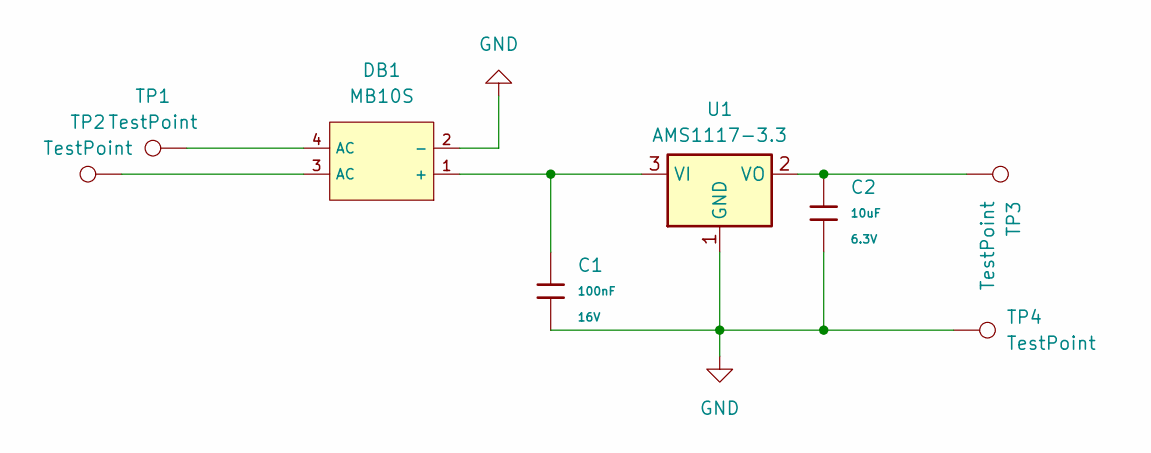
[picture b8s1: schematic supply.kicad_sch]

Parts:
C1: 100nF; C_0402; Voltage Rated 16V; Tolerance ±10%; Part CL05B104KO5NNNC; LCSC C1525
C2: 10uF; C_0402; Voltage Rated 6.3V; Tolerance ±20%; Part CL05A106MQ5NUNC; LCSC C15525
DB1: MB10S; MBS_L4.7-W3.8-P2.40-LS7.0-TL; Reverse Voltage (Vr) 1kV; Forward Voltage (Vf@If) 1.1V@400mA; Part MB10S-50MIL; LCSC C2488
TP1, TP2, TP3, TP4: TestPoint; TestPoint_THTPad_1.5x1.5mm_Drill0.7mm
U1: AMS1117-3.3; SOT-223-3_TabPin2

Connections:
GND: C1.2, C2.2, DB1.2 (-), TP4.1, U1.1 (GND)
unnamed: C1.1, DB1.1 (+), U1.3 (VI)
unnamed: DB1.3 (AC), TP2.1
unnamed: DB1.4 (AC), TP1.1
unnamed: C2.1, TP3.1, U1.2 (VO)
